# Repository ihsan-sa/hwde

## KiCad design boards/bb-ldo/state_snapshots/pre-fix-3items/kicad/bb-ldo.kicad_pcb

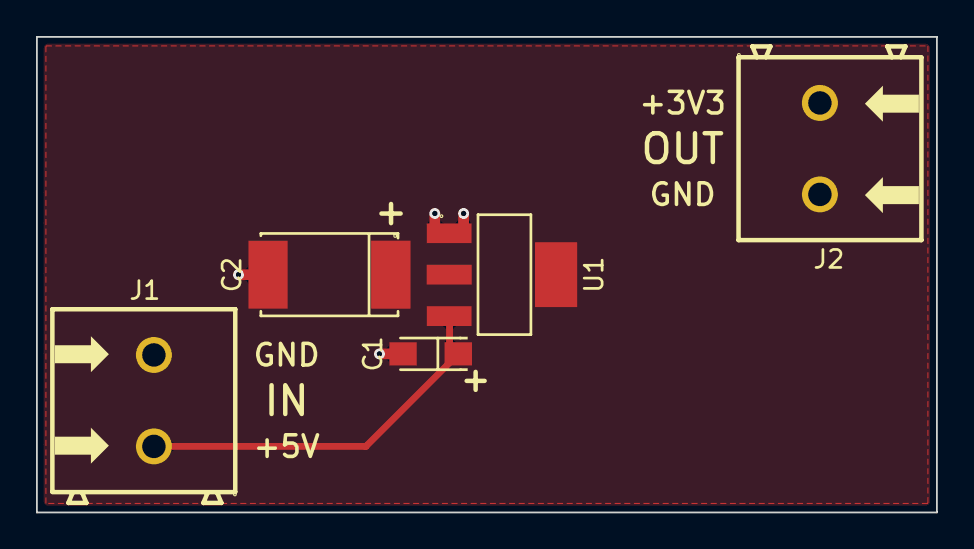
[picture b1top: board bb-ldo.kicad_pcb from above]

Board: 2 copper layers, 50.0 x 26.4 mm, 5 parts (0 on the bottom side), 3 nets.

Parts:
C1: 10uF 16V solid tantalum; CAP-SMD_L3.2-W1.6-RD-C7171
C2: 22uF 16V solid tantalum ESR 0.8ohm; CAP-SMD_L7.3-W4.3
J1, J2: 2P 5.08mm THT screw terminal; CONN-TH_2P-P5.00_WJ500V-5.08-2P
U1: AMS1117-3.3; SOT-223-3_L6.5-W3.4-P2.30-LS7.0-BR

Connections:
+3V3: C2.1, J2.1, U1.2, U1.4
+5V: C1.1, J1.1, U1.3
GND: C1.2, C2.2, J1.2, J2.2, U1.1

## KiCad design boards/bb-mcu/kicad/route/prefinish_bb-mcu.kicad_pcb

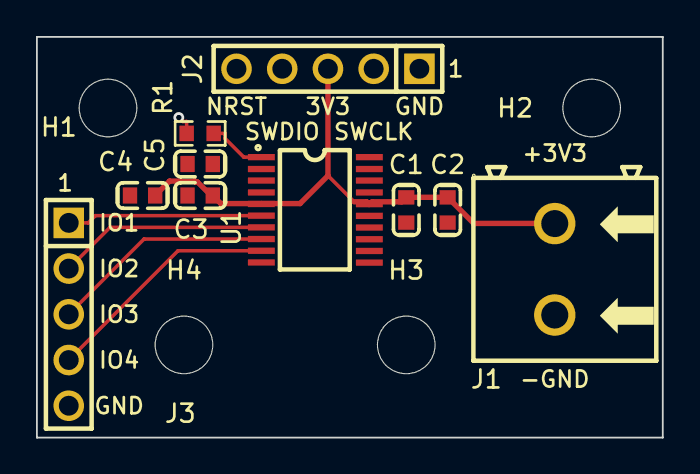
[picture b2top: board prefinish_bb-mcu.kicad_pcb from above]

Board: 2 copper layers, 34.8 x 22.3 mm, 14 parts (0 on the bottom side), 10 nets.

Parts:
C1, C5: 100nF 50V X7R; C0603
C2: 4.7uF 16V X7R; C0603
C3: 10nF 25V X7R; C0603
C4: 1uF 16V X7R; C0603
H1, H2, H3, H4: MountingHole_3.2mm_M3
J1: 2P 5.08mm screw terminal THT; CONN-TH_2P-P5.00_WJ500V-5.08-2P
J2, J3: 1x5 2.54mm male THT; HDR-TH_5P-P2.54-V-M
R1: 10k; R0603
U1: STM32F030F4P6TR; SOP-20_L6.5-W4.4-P0.65-LS6.4-BL

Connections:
+3V3: C1.1, C2.1, C3.1, C4.1, J1.1, J2.3, U1.5, U1.16
/BOOT0: R1.1, U1.1
/IO1: J3.1, U1.6
/IO2: J3.2, U1.7
/IO3: J3.3, U1.8
/IO4: J3.4, U1.9
/NRST: C5.1, J2.5, U1.4
/SWCLK: J2.2, U1.20
/SWDIO: J2.4, U1.19
GND: C1.2, C2.2, C3.2, C4.2, C5.2, J1.2, J2.1, J3.5, R1.2, U1.15

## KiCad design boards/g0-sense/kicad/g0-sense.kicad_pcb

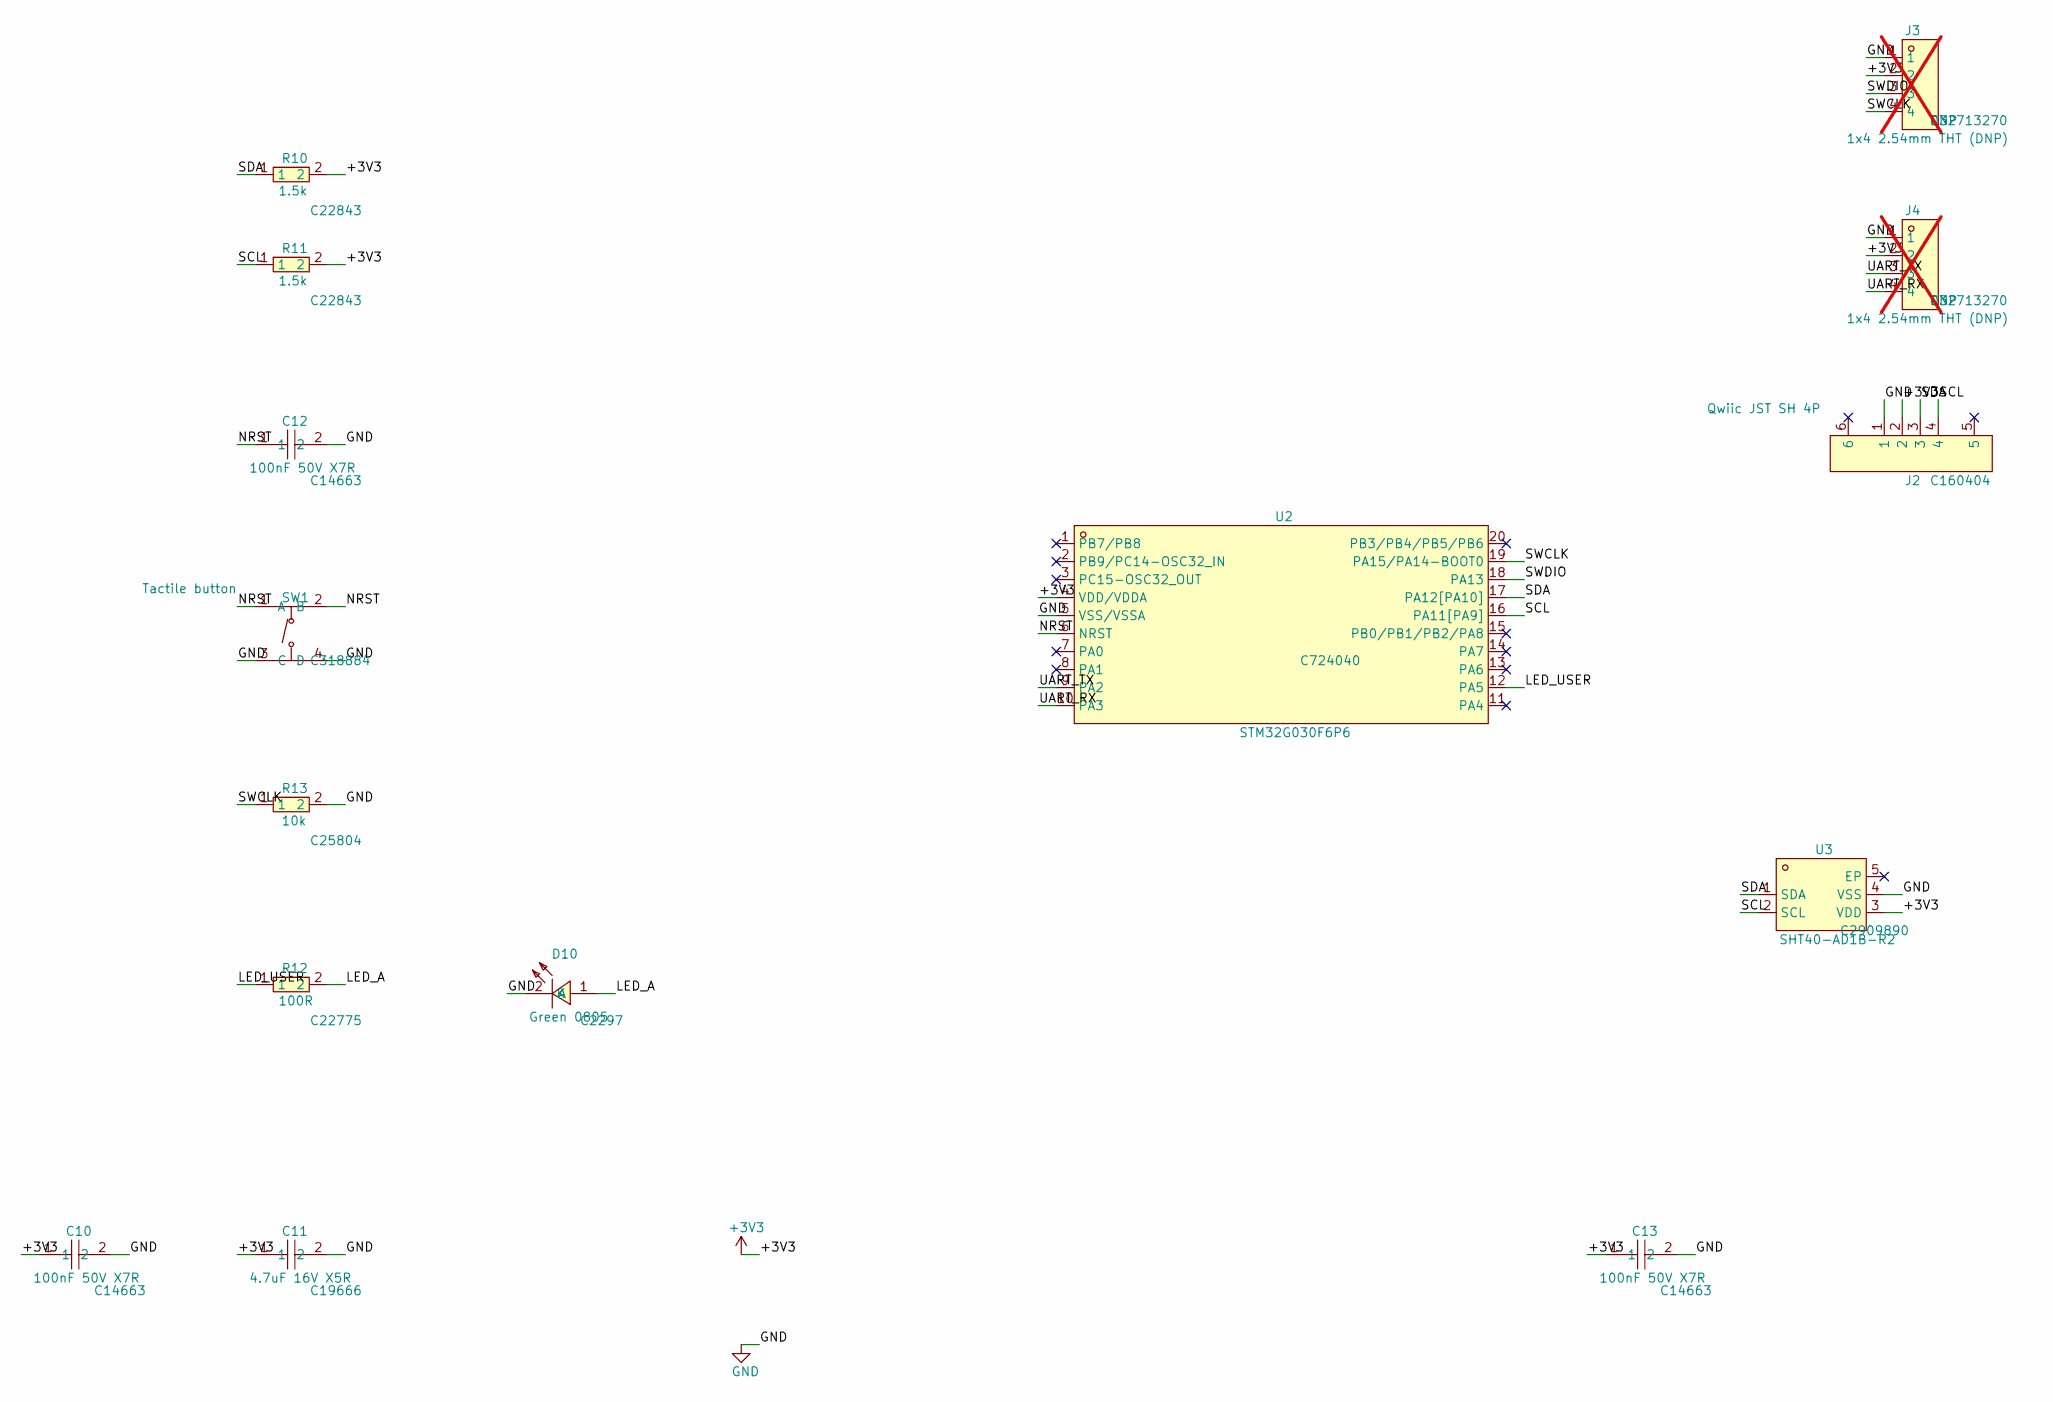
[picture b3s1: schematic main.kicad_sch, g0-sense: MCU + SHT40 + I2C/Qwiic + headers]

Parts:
C10, C12, C13: 100nF 50V X7R; C0603; LCSC C14663
C11: 4.7uF 16V X5R; C0603; LCSC C19666
D10: Green 0805; LED0805-R-RD; LCSC C2297
J2: Qwiic JST SH 4P; CONN-SMD_4P-P1.00_SM04B-SRSS-TB-LF-SN; LCSC C160404
J3, J4: 1x4 2.54mm THT (DNP); HDR-TH_4P-P2.54-V-M; LCSC C32713270; not fitted
R10, R11: 1.5k; R0603; LCSC C22843
R12: 100R; R0603; LCSC C22775
R13: 10k; R0603; LCSC C25804
SW1: Tactile button; SW-SMD_4P-L5.1-W5.1-P3.70-LS6.5-TL_H1.5; LCSC C318884
U2: STM32G030F6P6; TSSOP-20_L6.5-W4.4-P0.65-LS6.4-BL; LCSC C724040
U3: SHT40-AD1B-R2; DFN-4_L1.5-W1.5-P0.8-TL-EP; LCSC C2909890

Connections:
+3V3: C10.1, C11.1, C13.1, J2.2, J3.2, J4.2, R10.2, R11.2, U2.4 (VDD/VDDA), U3.3 (VDD); also elsewhere on the board
/main/LED_A: D10.1 (A), R12.2
/main/LED_USER: R12.1, U2.12 (PA5)
/main/NRST: C12.1, SW1.1 (A), SW1.2 (B), U2.6 (NRST)
/main/SCL: J2.4, R11.1, U2.16 (PA11[PA9]), U3.2 (SCL)
/main/SDA: J2.3, R10.1, U2.17 (PA12[PA10]), U3.1 (SDA)
/main/SWCLK: J3.4, R13.1, U2.19 (PA15/PA14-BOOT0)
/main/SWDIO: J3.3, U2.18 (PA13)
/main/UART_RX: J4.4, U2.10 (PA3)
/main/UART_TX: J4.3, U2.9 (PA2)
GND: C10.2, C11.2, C12.2, C13.2, D10.2 (K), J2.1, J3.1, J4.1, R13.2, SW1.3 (C), SW1.4 (D), U2.5 (VSS/VSSA), U3.4 (VSS); also elsewhere on the board

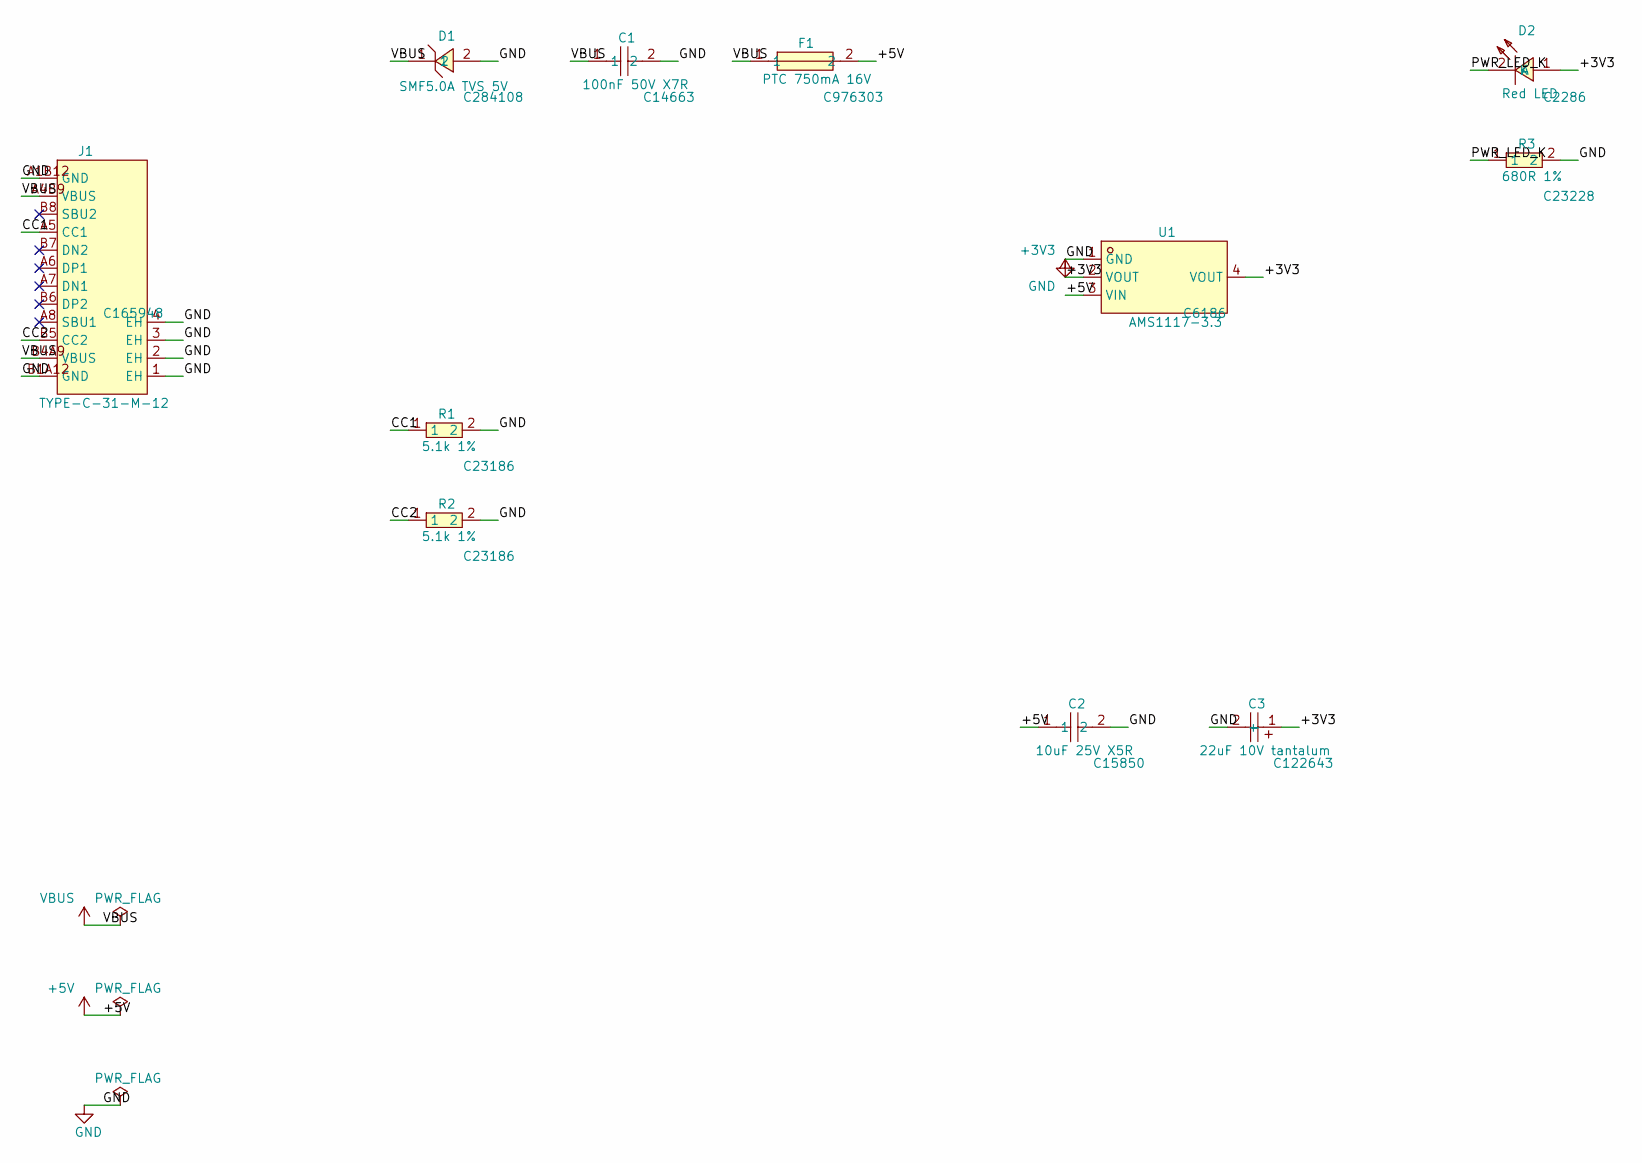
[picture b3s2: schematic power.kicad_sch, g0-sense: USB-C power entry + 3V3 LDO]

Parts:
C1: 100nF 50V X7R; C0603; LCSC C14663
C2: 10uF 25V X5R; C0805; LCSC C15850
C3: 22uF 10V tantalum; CASE-A_3216; LCSC C122643
D1: SMF5.0A TVS 5V; SOD-123_L2.8-W1.8-LS3.7-RD; LCSC C284108
D2: Red LED; LED-SMD_L1.6-W0.8-R-RD; LCSC C2286
F1: PTC 750mA 16V; F0805; LCSC C976303
J1: TYPE-C-31-M-12; USB-C_SMD-TYPE-C-31-M-12_1; LCSC C165948
R1, R2: 5.1k 1%; R0603; LCSC C23186
R3: 680R 1%; R0603; LCSC C23228
U1: AMS1117-3.3; SOT-223-3_L6.5-W3.4-P2.30-LS7.0-BR; LCSC C6186

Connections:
+3V3: C3.1 (+), D2.1 (A), U1.2 (VOUT), U1.4 (VOUT); also elsewhere on the board
+5V: C2.1, F1.2, U1.3 (VIN)
/power/CC1: J1.A5 (CC1), R1.1
/power/CC2: J1.B5 (CC2), R2.1
/power/PWR_LED_K: D2.2 (K), R3.1
GND: C1.2, C2.2, C3.2 (-), D1.2, J1.1 (EH), J1.2 (EH), J1.3 (EH), J1.4 (EH), J1.A1B12 (GND), J1.B1A12 (GND), R1.2, R2.2, R3.2, U1.1 (GND); also elsewhere on the board
VBUS: C1.1, D1.1, F1.1, J1.A4B9 (VBUS), J1.B4A9 (VBUS)

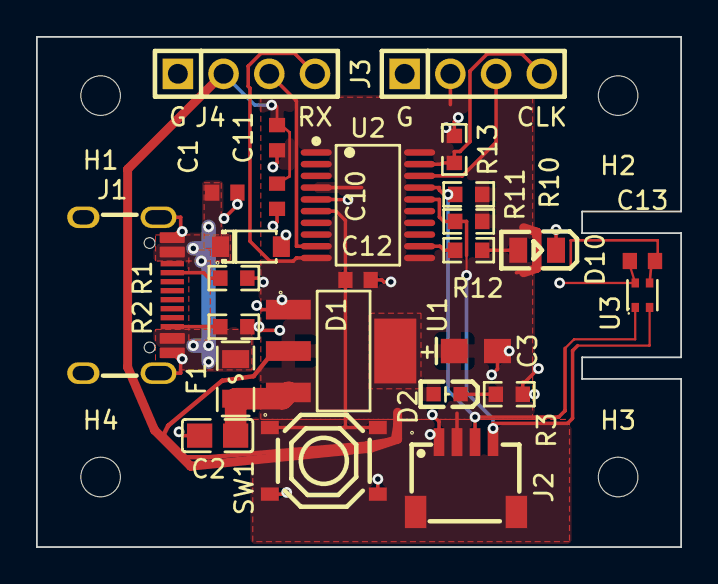
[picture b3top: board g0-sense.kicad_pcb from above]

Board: 2 copper layers, 35.8 x 28.3 mm, 30 parts (0 on the bottom side), 16 nets.

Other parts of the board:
H1, H2, H3, H4: MountingHole_2.2mm_M2
